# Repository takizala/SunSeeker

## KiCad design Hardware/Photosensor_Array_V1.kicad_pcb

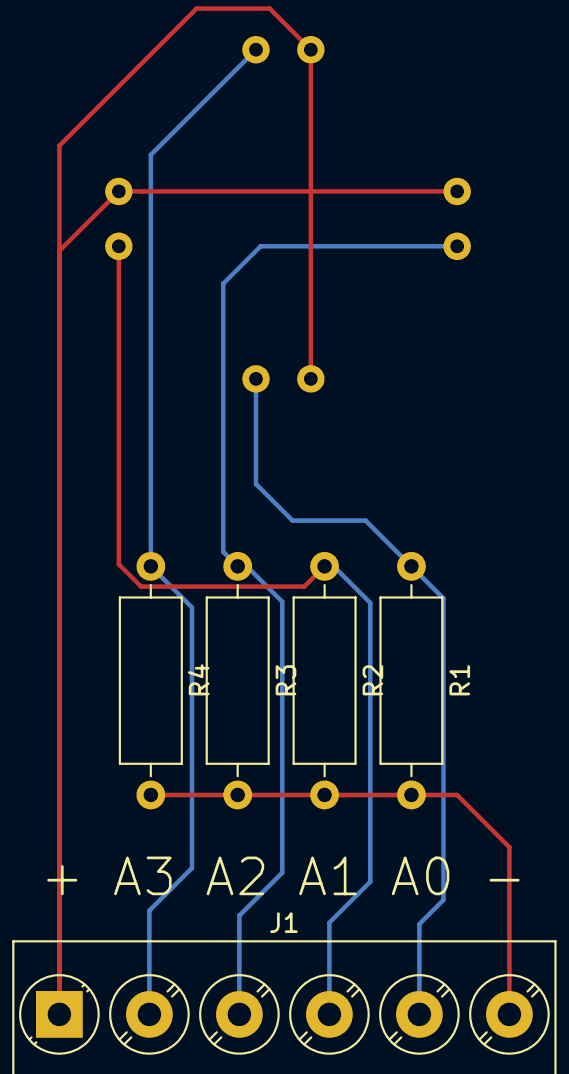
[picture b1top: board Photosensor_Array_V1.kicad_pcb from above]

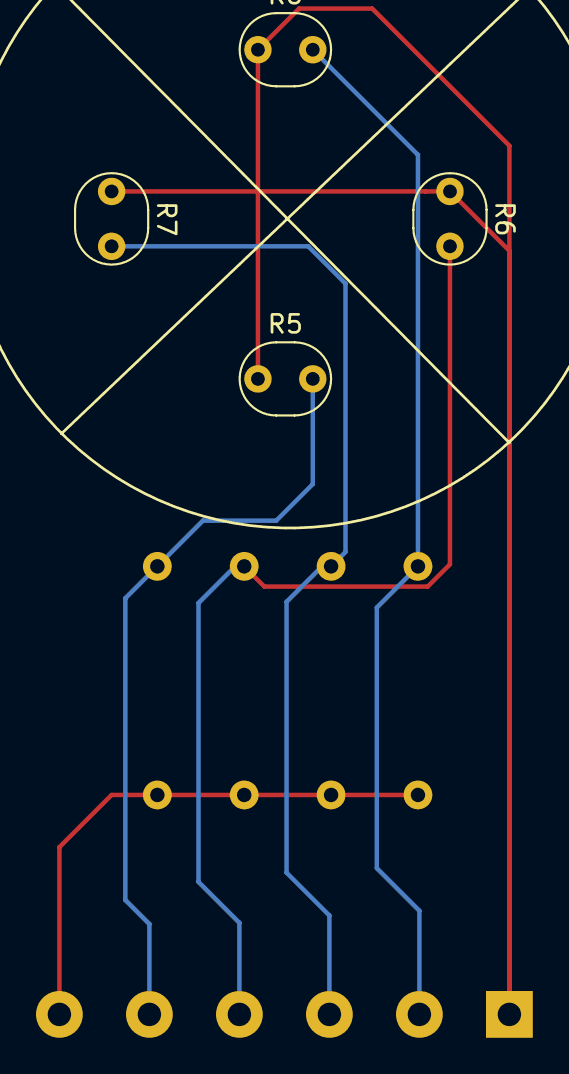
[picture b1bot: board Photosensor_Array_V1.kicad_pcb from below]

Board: 2 copper layers, 9 parts (4 on the bottom side), 6 nets.

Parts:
J1: 1x6 Screw Terminal; TerminalBlock_Phoenix_PT-1,5-6-5.0-H_1x06_P5.00mm_Horizontal
R1, R2, R3, R4: R; R_Axial_DIN0309_L9.0mm_D3.2mm_P12.70mm_Horizontal
R5, R6, R7, R8: R_PHOTO; 5mmPhotoresistor

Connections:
unnamed: J1.1, R5.1, R6.1, R7.1, R8.1
unnamed: J1.2, R4.1, R8.2
unnamed: J1.3, R3.1, R7.2
unnamed: J1.4, R2.1, R6.2
unnamed: J1.5, R1.1, R5.2
unnamed: J1.6, R1.2, R2.2, R3.2, R4.2

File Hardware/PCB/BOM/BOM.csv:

Reference, Quantity, Value, Footprint, Datasheet,Digi-Key PN,Price
J1 ,1,1x6 Female Header,Connector_PinSocket_2.00mm:PinSocket_1x06_P2.00mm_Vertical,https://media.digikey.com/pdf/Data%20Sheets/Adafruit%20PDFs/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,311-10.0KHRDKR-ND,$1.95 
R1 R2 R3 R4 ,4,R,Resistor_SMD:R_0603_1608Metric_Pad0.98x0.95mm_HandSolder,https://www.yageo.com/upload/media/product/productsearch/dat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,1528-1074-ND,$0.00 
R5 R6 R7 R8 ,4,R_PHOTO,photoresistor5mm:5mmPhotoresistor,~,~,~

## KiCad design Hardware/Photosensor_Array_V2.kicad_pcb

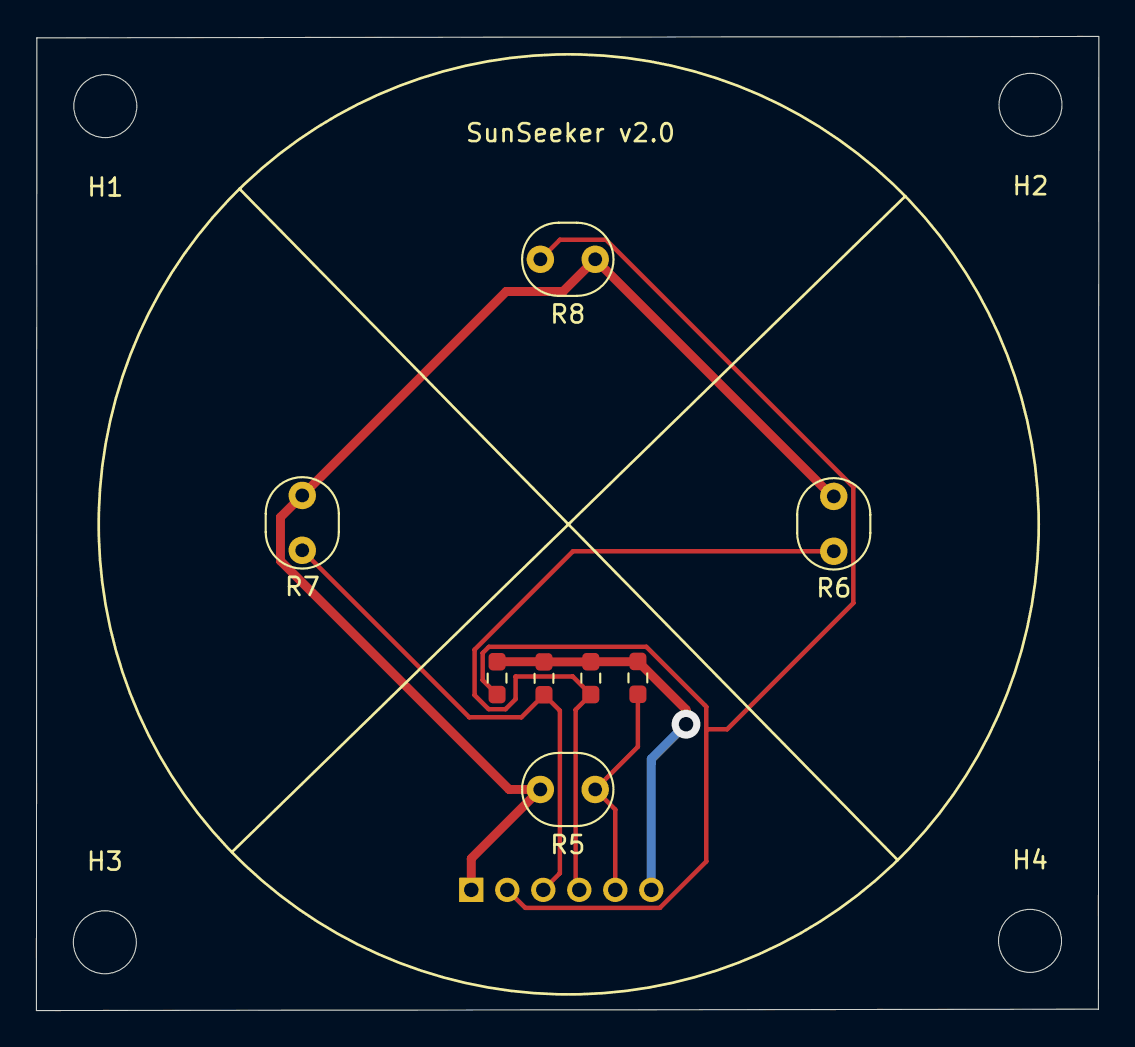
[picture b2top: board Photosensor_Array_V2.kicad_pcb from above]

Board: 2 copper layers, 59.0 x 54.1 mm, 13 parts (1 on the bottom side), 6 nets.

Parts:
H1, H2, H3, H4: MountingHole_3.5mm
J1: 1x6 Female Header; PinSocket_1x06_P2.00mm_Vertical
R1, R2, R3, R4: R; R_0603_1608Metric_Pad0.98x0.95mm_HandSolder
R5, R6, R7, R8: R_PHOTO; 5mmPhotoresistor

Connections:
unnamed: J1.1, R5.1, R6.1, R7.1, R8.1
unnamed: J1.2, R1.1, R8.2
unnamed: J1.3, R2.1, R7.2
unnamed: J1.4, R3.1, R6.2
unnamed: J1.5, R4.1, R5.2
unnamed: J1.6, R1.2, R2.2, R3.2, R4.2

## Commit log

2021-11-01 added CAD
2021-11-02 Add files via upload
    Uploaded the first version for LDR sensor
2021-11-02 Create Gerber
